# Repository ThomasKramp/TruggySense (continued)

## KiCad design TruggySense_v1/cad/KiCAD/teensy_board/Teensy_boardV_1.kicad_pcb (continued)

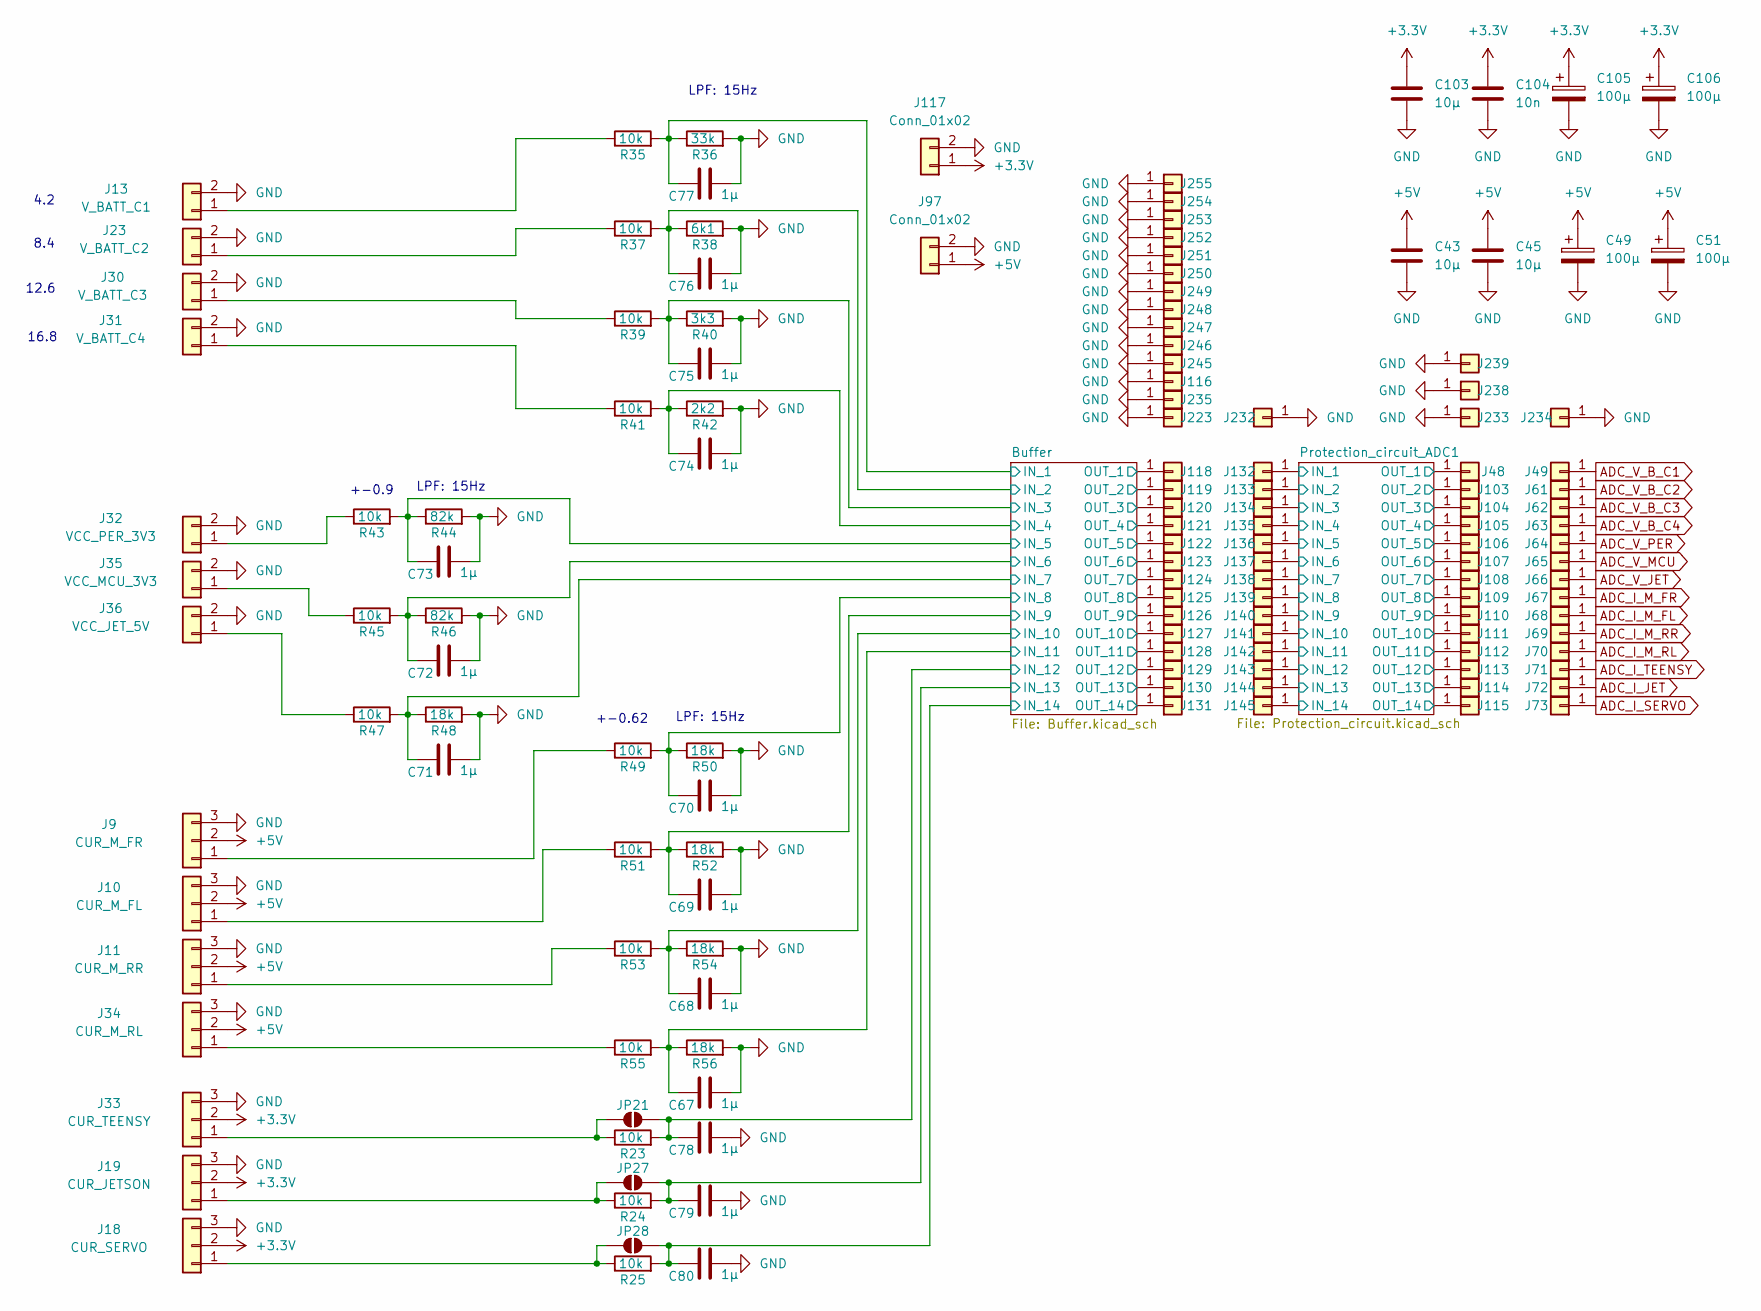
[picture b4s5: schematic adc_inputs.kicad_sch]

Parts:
C43, C45, C103: 10µ; C_0805_2012Metric_Pad1.18x1.45mm_HandSolder
C49, C51, C105, C106: 100µ; CP_Radial_D5.0mm_P2.00mm
C67, C68, C69, C70, C71, C72, C73, C74, C75, C76, C77, C78, C79, C80: 1µ; C_0805_2012Metric_Pad1.18x1.45mm_HandSolder
C104: 10n; C_0805_2012Metric_Pad1.18x1.45mm_HandSolder
J9: CUR_M_FR; PinHeader_1x03_P2.54mm_Vertical
J10: CUR_M_FL; PinHeader_1x03_P2.54mm_Vertical
J11: CUR_M_RR; PinHeader_1x03_P2.54mm_Vertical
J13: V_BATT_C1; PinSocket_1x02_P2.54mm_Vertical
J18: CUR_SERVO; PinHeader_1x03_P2.54mm_Vertical
J19: CUR_JETSON; PinHeader_1x03_P2.54mm_Vertical
J23: V_BATT_C2; PinSocket_1x02_P2.54mm_Vertical
J30: V_BATT_C3; PinSocket_1x02_P2.54mm_Vertical
J31: V_BATT_C4; PinSocket_1x02_P2.54mm_Vertical
J32: VCC_PER_3V3; PinSocket_1x02_P2.54mm_Vertical
J33: CUR_TEENSY; PinHeader_1x03_P2.54mm_Vertical
J34: CUR_M_RL; PinHeader_1x03_P2.54mm_Vertical
J35: VCC_MCU_3V3; PinSocket_1x02_P2.54mm_Vertical
J36: VCC_JET_5V; PinSocket_1x02_P2.54mm_Vertical
J48, J49, J61, J62, J63, J64, J65, J66, J67, J68, J69, J70, J71, J72, J73, J103, J104, J105, J106, J107, J108, J109, J110, J111, J112, J113, J114, J115, J116, J118, J119, J120, J121, J122, J123, J124, J125, J126, J127, J128, J129, J130, J131, J132, J133, J134, J135, J136, J137, J138, J139, J140, J141, J142, J143, J144, J145, J223, J232, J233, J234, J235, J238, J239, J245, J246, J247, J248, J249, J250, J251, J252, J253, J254, J255: Conn_01x01; PinHeader_1x01_P2.54mm_Vertical
J97, J117: Conn_01x02; PinSocket_1x02_P2.54mm_Vertical
JP21, JP27, JP28: SolderJumper_2_Open; SolderJumper-2_P1.3mm_Open_RoundedPad1.0x1.5mm
R23, R24, R25, R35, R37, R39, R41, R43, R45, R47, R49, R51, R53, R55: 10k; R_0805_2012Metric_Pad1.20x1.40mm_HandSolder
R36: 33k; R_0805_2012Metric_Pad1.20x1.40mm_HandSolder
R38: 6k1; R_0805_2012Metric_Pad1.20x1.40mm_HandSolder
R40: 3k3; R_0805_2012Metric_Pad1.20x1.40mm_HandSolder
R42: 2k2; R_0805_2012Metric_Pad1.20x1.40mm_HandSolder
R44, R46: 82k; R_0805_2012Metric_Pad1.20x1.40mm_HandSolder
R48, R50, R52, R54, R56: 18k; R_0805_2012Metric_Pad1.20x1.40mm_HandSolder

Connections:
+5V: C43.1, C45.1, C49.1, C51.1, J9.2, J10.2, J11.2, J34.2, J97.1; also elsewhere on the board
/ADC inputs/Buffer/IN_1: C77.2, R35.2, R36.1; also elsewhere on the board
/ADC inputs/Buffer/IN_2: C76.2, R37.2, R38.1; also elsewhere on the board
/ADC inputs/Buffer/IN_3: C75.2, R39.2, R40.1; also elsewhere on the board
/ADC inputs/Buffer/IN_4: C74.2, R41.2, R42.1; also elsewhere on the board
/ADC inputs/Buffer/IN_5: C73.2, R43.2, R44.1; also elsewhere on the board
/ADC inputs/Buffer/IN_6: C72.2, R45.2, R46.1; also elsewhere on the board
/ADC inputs/Buffer/IN_7: C71.2, R47.2, R48.1; also elsewhere on the board
/ADC inputs/Buffer/IN_8: C70.2, R49.2, R50.1; also elsewhere on the board
/ADC inputs/Buffer/IN_9: C69.2, R51.2, R52.1; also elsewhere on the board
/ADC inputs/Buffer/IN_10: C68.2, R53.2, R54.1; also elsewhere on the board
/ADC inputs/Buffer/IN_11: C67.2, R55.2, R56.1; also elsewhere on the board
/ADC inputs/Buffer/IN_12: C78.2, JP21.2 (B), R23.2; also elsewhere on the board
/ADC inputs/Buffer/IN_13: C79.2, JP27.2 (B), R24.2; also elsewhere on the board
/ADC inputs/Buffer/IN_14: C80.2, JP28.2 (B), R25.2; also elsewhere on the board
/ADC inputs/Buffer/OUT_1: J118.1; also elsewhere on the board
/ADC inputs/Buffer/OUT_2: J119.1; also elsewhere on the board
/ADC inputs/Buffer/OUT_3: J120.1; also elsewhere on the board
/ADC inputs/Buffer/OUT_4: J121.1; also elsewhere on the board
/ADC inputs/Buffer/OUT_5: J122.1; also elsewhere on the board
/ADC inputs/Buffer/OUT_6: J123.1; also elsewhere on the board
/ADC inputs/Buffer/OUT_7: J124.1; also elsewhere on the board
/ADC inputs/Buffer/OUT_8: J125.1; also elsewhere on the board
/ADC inputs/Buffer/OUT_9: J126.1; also elsewhere on the board
/ADC inputs/Buffer/OUT_10: J127.1; also elsewhere on the board
/ADC inputs/Buffer/OUT_11: J128.1; also elsewhere on the board
/ADC inputs/Buffer/OUT_12: J129.1; also elsewhere on the board
/ADC inputs/Buffer/OUT_13: J130.1; also elsewhere on the board
/ADC inputs/Buffer/OUT_14: J131.1; also elsewhere on the board
/ADC inputs/Protection_circuit_ADC1/IN_1: J132.1; also elsewhere on the board
/ADC inputs/Protection_circuit_ADC1/IN_2: J133.1; also elsewhere on the board
/ADC inputs/Protection_circuit_ADC1/IN_3: J134.1; also elsewhere on the board
/ADC inputs/Protection_circuit_ADC1/IN_4: J135.1; also elsewhere on the board
/ADC inputs/Protection_circuit_ADC1/IN_5: J136.1; also elsewhere on the board
/ADC inputs/Protection_circuit_ADC1/IN_6: J137.1; also elsewhere on the board
/ADC inputs/Protection_circuit_ADC1/IN_7: J138.1; also elsewhere on the board
/ADC inputs/Protection_circuit_ADC1/IN_8: J139.1; also elsewhere on the board
/ADC inputs/Protection_circuit_ADC1/IN_9: J140.1; also elsewhere on the board
/ADC inputs/Protection_circuit_ADC1/IN_10: J141.1; also elsewhere on the board
/ADC inputs/Protection_circuit_ADC1/IN_11: J142.1; also elsewhere on the board
/ADC inputs/Protection_circuit_ADC1/IN_12: J143.1; also elsewhere on the board
/ADC inputs/Protection_circuit_ADC1/IN_13: J144.1; also elsewhere on the board
/ADC inputs/Protection_circuit_ADC1/IN_14: J145.1; also elsewhere on the board
/ADC inputs/Protection_circuit_ADC1/OUT_1: J48.1; also elsewhere on the board
/ADC inputs/Protection_circuit_ADC1/OUT_2: J103.1; also elsewhere on the board
/ADC inputs/Protection_circuit_ADC1/OUT_3: J104.1; also elsewhere on the board
/ADC inputs/Protection_circuit_ADC1/OUT_4: J105.1; also elsewhere on the board
/ADC inputs/Protection_circuit_ADC1/OUT_5: J106.1; also elsewhere on the board
/ADC inputs/Protection_circuit_ADC1/OUT_6: J107.1; also elsewhere on the board
/ADC inputs/Protection_circuit_ADC1/OUT_7: J108.1; also elsewhere on the board
/ADC inputs/Protection_circuit_ADC1/OUT_8: J109.1; also elsewhere on the board
/ADC inputs/Protection_circuit_ADC1/OUT_9: J110.1; also elsewhere on the board
/ADC inputs/Protection_circuit_ADC1/OUT_10: J111.1; also elsewhere on the board
/ADC inputs/Protection_circuit_ADC1/OUT_11: J112.1; also elsewhere on the board
/ADC inputs/Protection_circuit_ADC1/OUT_12: J113.1; also elsewhere on the board
/ADC inputs/Protection_circuit_ADC1/OUT_13: J114.1; also elsewhere on the board
/ADC inputs/Protection_circuit_ADC1/OUT_14: J115.1; also elsewhere on the board
ADC_I_JET: J72.1; also elsewhere on the board
ADC_I_M_FL: J68.1; also elsewhere on the board
ADC_I_M_FR: J67.1; also elsewhere on the board
ADC_I_M_RL: J70.1; also elsewhere on the board
ADC_I_M_RR: J69.1; also elsewhere on the board
ADC_I_SERVO: J73.1; also elsewhere on the board
ADC_I_TEENSY: J71.1; also elsewhere on the board
ADC_V_B_C1: J49.1; also elsewhere on the board
ADC_V_B_C2: J61.1; also elsewhere on the board
ADC_V_B_C3: J62.1; also elsewhere on the board
ADC_V_B_C4: J63.1; also elsewhere on the board
ADC_V_JET: J66.1; also elsewhere on the board
ADC_V_MCU: J65.1; also elsewhere on the board
ADC_V_PER: J64.1; also elsewhere on the board
GND: C43.2, C45.2, C49.2, C51.2, C67.1, C68.1, C69.1, C70.1, C71.1, C72.1, C73.1, C74.1, C75.1, C76.1, C77.1, C78.1, C79.1, C80.1, C103.2, C104.2, C105.2, C106.2, J9.3, J10.3, J11.3, J13.2, J18.3, J19.3, J23.2, J30.2, J31.2, J32.2, J33.3, J34.3, J35.2, J36.2, J97.2, J116.1, J117.2, J223.1, J232.1, J233.1, J234.1, J235.1, J238.1, J239.1, J245.1, J246.1, J247.1, J248.1, J249.1, J250.1, J251.1, J252.1, J253.1, J254.1, J255.1, R36.2, R38.2, R40.2, R42.2, R44.2, R46.2, R48.2, R50.2, R52.2, R54.2, R56.2; also elsewhere on the board
unnamed: J9.1, R49.1
unnamed: J10.1, R51.1
unnamed: J11.1, R53.1
unnamed: J13.1, R35.1
unnamed: J18.1, JP28.1 (A), R25.1
unnamed: J19.1, JP27.1 (A), R24.1
unnamed: J23.1, R37.1
unnamed: J30.1, R39.1
unnamed: J31.1, R41.1
unnamed: J32.1, R43.1
unnamed: J33.1, JP21.1 (A), R23.1
unnamed: J34.1, R55.1
unnamed: J35.1, R45.1
unnamed: J36.1, R47.1

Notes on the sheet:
+-0.62
LPF: 15Hz
+-0.9
12.6
16.8
4.2
8.4

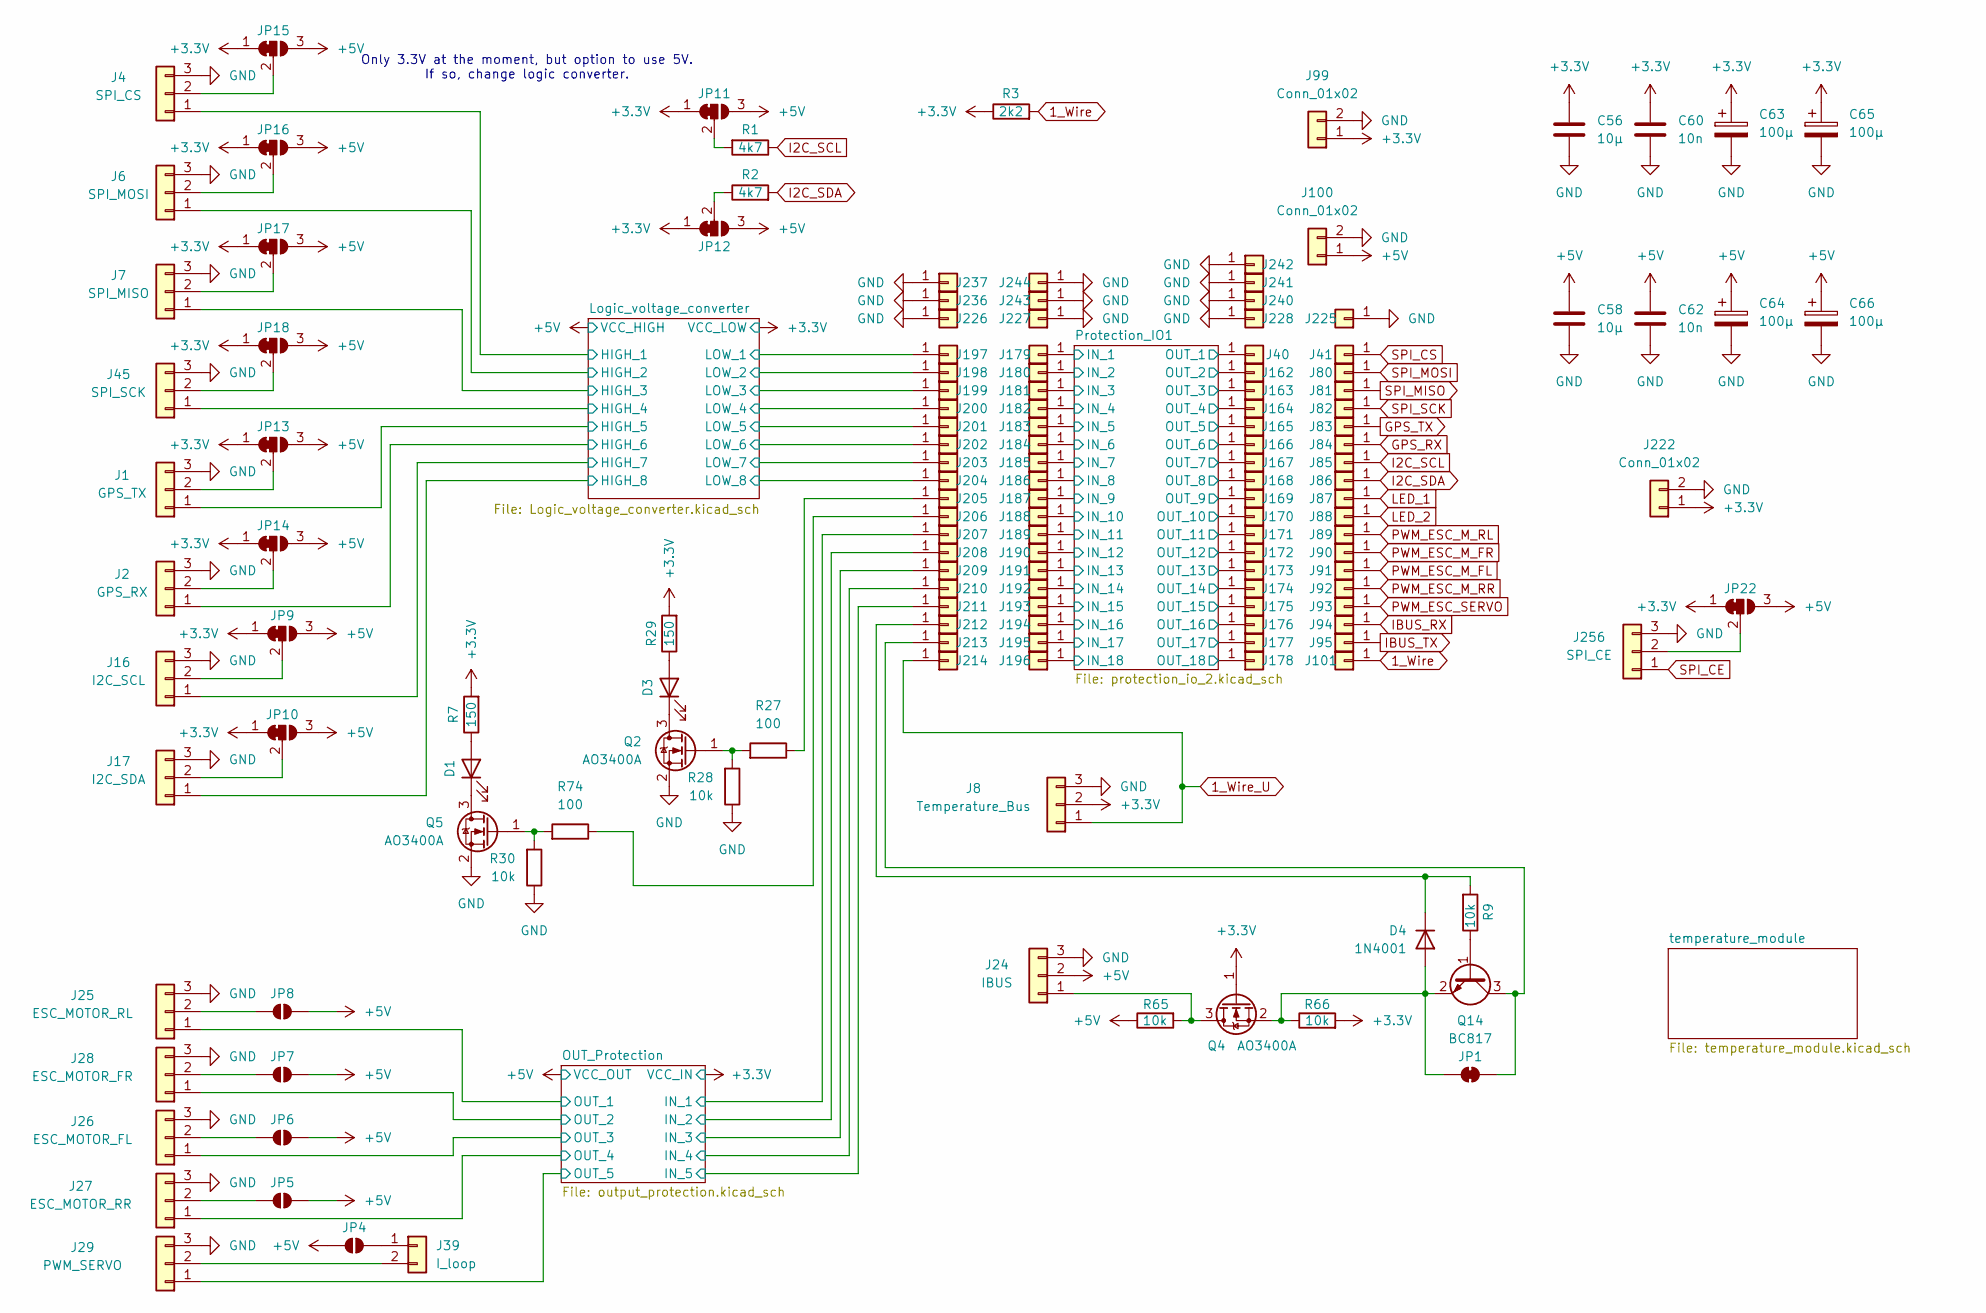
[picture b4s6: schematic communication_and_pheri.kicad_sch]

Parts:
C56, C58: 10µ; C_0805_2012Metric_Pad1.18x1.45mm_HandSolder
C60, C62: 10n; C_0805_2012Metric_Pad1.18x1.45mm_HandSolder
C63, C64, C65, C66: 100µ; CP_Radial_D5.0mm_P2.00mm
D1, D3: LED; LED_0805_2012Metric_Pad1.15x1.40mm_HandSolder
D4: 1N4001; D_SMA_Handsoldering
J1: GPS_TX; PinHeader_1x03_P2.54mm_Vertical
J2: GPS_RX; PinHeader_1x03_P2.54mm_Vertical
J4: SPI_CS; PinHeader_1x03_P2.54mm_Vertical
J6: SPI_MOSI; PinHeader_1x03_P2.54mm_Vertical
J7: SPI_MISO; PinHeader_1x03_P2.54mm_Vertical
J8: Temperature_Bus; PinHeader_1x03_P2.54mm_Vertical
J16: I2C_SCL; PinHeader_1x03_P2.54mm_Vertical
J17: I2C_SDA; PinHeader_1x03_P2.54mm_Vertical
J24: IBUS; PinHeader_1x03_P2.54mm_Vertical
J25: ESC_MOTOR_RL; PinHeader_1x03_P2.54mm_Vertical
J26: ESC_MOTOR_FL; PinHeader_1x03_P2.54mm_Vertical
J27: ESC_MOTOR_RR; PinHeader_1x03_P2.54mm_Vertical
J28: ESC_MOTOR_FR; PinHeader_1x03_P2.54mm_Vertical
J29: PWM_SERVO; PinHeader_1x03_P2.54mm_Vertical
J39: I_loop; PinSocket_1x02_P2.54mm_Vertical
J40, J41, J80, J81, J82, J83, J84, J85, J86, J87, J88, J89, J90, J91, J92, J93, J94, J95, J101, J162, J163, J164, J165, J166, J167, J168, J169, J170, J171, J172, J173, J174, J175, J176, J177, J178, J179, J180, J181, J182, J183, J184, J185, J186, J187, J188, J189, J190, J191, J192, J193, J194, J195, J196, J197, J198, J199, J200, J201, J202, J203, J204, J205, J206, J207, J208, J209, J210, J211, J212, J213, J214, J225, J226, J227, J228, J236, J237, J240, J241, J242, J243, J244: Conn_01x01; PinHeader_1x01_P2.54mm_Vertical
J45: SPI_SCK; PinHeader_1x03_P2.54mm_Vertical
J99, J100, J222: Conn_01x02; PinSocket_1x02_P2.54mm_Vertical
J256: SPI_CE; PinHeader_1x03_P2.54mm_Vertical
JP1: SolderJumper_2_Bridged; SolderJumper-2_P1.3mm_Bridged_RoundedPad1.0x1.5mm
JP4, JP5, JP6, JP7, JP8: SolderJumper_2_Bridged; SolderJumper-2_P1.3mm_Open_RoundedPad1.0x1.5mm
JP9, JP10, JP11, JP12, JP13, JP14, JP15, JP16, JP17, JP18, JP22: SolderJumper_3_Bridged12; SolderJumper-3_P1.3mm_Bridged12_RoundedPad1.0x1.5mm
Q2, Q4, Q5: AO3400A; SOT-23
Q14: BC817; SOT-23
R1, R2: 4k7; R_0805_2012Metric_Pad1.20x1.40mm_HandSolder
R3: 2k2; R_0805_2012Metric_Pad1.20x1.40mm_HandSolder
R7, R29: 150; R_0805_2012Metric_Pad1.20x1.40mm_HandSolder
R9, R28, R30, R65, R66: 10k; R_0805_2012Metric_Pad1.20x1.40mm_HandSolder
R27, R74: 100; R_0805_2012Metric_Pad1.20x1.40mm_HandSolder

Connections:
1_Wire: J101.1, R3.2; also elsewhere on the board
1_Wire_U: J8.1, J214.1; also elsewhere on the board
+5V: C58.1, C62.1, C64.1, C66.1, J24.2, J100.1, J256.2, JP4.1 (A), JP5.2 (B), JP6.2 (B), JP7.2 (B), JP8.2 (B), JP9.3 (B), JP10.3 (B), JP11.3 (B), JP12.3 (B), JP13.3 (B), JP14.3 (B), JP15.3 (B), JP16.3 (B), JP17.3 (B), JP18.3 (B), JP22.2 (B), JP22.3 (B), R65.1; also elsewhere on the board
/Communication & pheripherals/Logic_voltage_converter/HIGH_1: J4.1; also elsewhere on the board
/Communication & pheripherals/Logic_voltage_converter/HIGH_2: J6.1; also elsewhere on the board
/Communication & pheripherals/Logic_voltage_converter/HIGH_3: J7.1; also elsewhere on the board
/Communication & pheripherals/Logic_voltage_converter/HIGH_4: J45.1; also elsewhere on the board
/Communication & pheripherals/Logic_voltage_converter/HIGH_5: J1.1; also elsewhere on the board
/Communication & pheripherals/Logic_voltage_converter/HIGH_6: J2.1; also elsewhere on the board
/Communication & pheripherals/Logic_voltage_converter/HIGH_7: J16.1; also elsewhere on the board
/Communication & pheripherals/Logic_voltage_converter/HIGH_8: J17.1; also elsewhere on the board
/Communication & pheripherals/Logic_voltage_converter/LOW_1: J197.1; also elsewhere on the board
/Communication & pheripherals/Logic_voltage_converter/LOW_2: J198.1; also elsewhere on the board
/Communication & pheripherals/Logic_voltage_converter/LOW_3: J199.1; also elsewhere on the board
/Communication & pheripherals/Logic_voltage_converter/LOW_4: J200.1; also elsewhere on the board
/Communication & pheripherals/Logic_voltage_converter/LOW_5: J201.1; also elsewhere on the board
/Communication & pheripherals/Logic_voltage_converter/LOW_6: J202.1; also elsewhere on the board
/Communication & pheripherals/Logic_voltage_converter/LOW_7: J203.1; also elsewhere on the board
/Communication & pheripherals/Logic_voltage_converter/LOW_8: J204.1; also elsewhere on the board
/Communication & pheripherals/OUT_Protection/IN_1: J207.1; also elsewhere on the board
/Communication & pheripherals/OUT_Protection/IN_2: J208.1; also elsewhere on the board
/Communication & pheripherals/OUT_Protection/IN_3: J209.1; also elsewhere on the board
/Communication & pheripherals/OUT_Protection/IN_4: J210.1; also elsewhere on the board
/Communication & pheripherals/OUT_Protection/IN_5: J211.1; also elsewhere on the board
/Communication & pheripherals/OUT_Protection/OUT_1: J25.1; also elsewhere on the board
/Communication & pheripherals/OUT_Protection/OUT_2: J28.1; also elsewhere on the board
/Communication & pheripherals/OUT_Protection/OUT_3: J26.1; also elsewhere on the board
/Communication & pheripherals/OUT_Protection/OUT_4: J27.1; also elsewhere on the board
/Communication & pheripherals/OUT_Protection/OUT_5: J29.1; also elsewhere on the board
/Communication & pheripherals/Protection_IO1/IN_1: J179.1; also elsewhere on the board
/Communication & pheripherals/Protection_IO1/IN_2: J180.1; also elsewhere on the board
/Communication & pheripherals/Protection_IO1/IN_3: J181.1; also elsewhere on the board
/Communication & pheripherals/Protection_IO1/IN_4: J182.1; also elsewhere on the board
/Communication & pheripherals/Protection_IO1/IN_5: J183.1; also elsewhere on the board
/Communication & pheripherals/Protection_IO1/IN_6: J184.1; also elsewhere on the board
/Communication & pheripherals/Protection_IO1/IN_7: J185.1; also elsewhere on the board
/Communication & pheripherals/Protection_IO1/IN_8: J186.1; also elsewhere on the board
/Communication & pheripherals/Protection_IO1/IN_9: J187.1; also elsewhere on the board
/Communication & pheripherals/Protection_IO1/IN_10: J188.1; also elsewhere on the board
/Communication & pheripherals/Protection_IO1/IN_11: J189.1; also elsewhere on the board
/Communication & pheripherals/Protection_IO1/IN_12: J190.1; also elsewhere on the board
/Communication & pheripherals/Protection_IO1/IN_13: J191.1; also elsewhere on the board
/Communication & pheripherals/Protection_IO1/IN_14: J192.1; also elsewhere on the board
/Communication & pheripherals/Protection_IO1/IN_15: J193.1; also elsewhere on the board
/Communication & pheripherals/Protection_IO1/IN_16: J194.1; also elsewhere on the board
/Communication & pheripherals/Protection_IO1/IN_17: J195.1; also elsewhere on the board
/Communication & pheripherals/Protection_IO1/IN_18: J196.1; also elsewhere on the board
/Communication & pheripherals/Protection_IO1/OUT_1: J40.1; also elsewhere on the board
/Communication & pheripherals/Protection_IO1/OUT_2: J162.1; also elsewhere on the board
/Communication & pheripherals/Protection_IO1/OUT_3: J163.1; also elsewhere on the board
/Communication & pheripherals/Protection_IO1/OUT_4: J164.1; also elsewhere on the board
/Communication & pheripherals/Protection_IO1/OUT_5: J165.1; also elsewhere on the board
/Communication & pheripherals/Protection_IO1/OUT_6: J166.1; also elsewhere on the board
/Communication & pheripherals/Protection_IO1/OUT_7: J167.1; also elsewhere on the board
/Communication & pheripherals/Protection_IO1/OUT_8: J168.1; also elsewhere on the board
/Communication & pheripherals/Protection_IO1/OUT_9: J169.1; also elsewhere on the board
/Communication & pheripherals/Protection_IO1/OUT_10: J170.1; also elsewhere on the board
/Communication & pheripherals/Protection_IO1/OUT_11: J171.1; also elsewhere on the board
/Communication & pheripherals/Protection_IO1/OUT_12: J172.1; also elsewhere on the board
/Communication & pheripherals/Protection_IO1/OUT_13: J173.1; also elsewhere on the board
/Communication & pheripherals/Protection_IO1/OUT_14: J174.1; also elsewhere on the board
/Communication & pheripherals/Protection_IO1/OUT_15: J175.1; also elsewhere on the board
/Communication & pheripherals/Protection_IO1/OUT_16: J176.1; also elsewhere on the board
/Communication & pheripherals/Protection_IO1/OUT_17: J177.1; also elsewhere on the board
/Communication & pheripherals/Protection_IO1/OUT_18: J178.1; also elsewhere on the board
GND: C56.2, C58.2, C60.2, C62.2, C63.2, C64.2, C65.2, C66.2, J1.3, J2.3, J4.3, J6.3, J7.3, J8.3, J16.3, J17.3, J24.3, J25.3, J26.3, J27.3, J28.3, J29.3, J45.3, J99.2, J100.2, J222.2, J225.1, J226.1, J227.1, J228.1, J236.1, J237.1, J240.1, J241.1, J242.1, J243.1, J244.1, J256.3, Q2.2 (S), Q5.2 (S), R28.1, R30.1; also elsewhere on the board
GPS_RX: J84.1; also elsewhere on the board
GPS_TX: J83.1; also elsewhere on the board
I2C_SCL: J85.1, R1.1; also elsewhere on the board
I2C_SDA: J86.1, R2.2; also elsewhere on the board
IBUS_RX: J94.1; also elsewhere on the board
IBUS_TX: J95.1; also elsewhere on the board
unnamed: D1.2 (A), R7.1
unnamed: D1.1 (K), Q5.3 (D)
unnamed: D3.2 (A), R29.1
unnamed: D3.1 (K), Q2.3 (D)
unnamed: D4.2 (A), JP1.2 (B), Q4.2 (S), Q14.2 (E), R66.1
unnamed: D4.1 (K), J212.1, R9.2
unnamed: J1.2, JP13.2 (C)
unnamed: J2.2, JP14.2 (C)
unnamed: J4.2, JP15.2 (C)
unnamed: J6.2, JP16.2 (C)
unnamed: J7.2, JP17.2 (C)
unnamed: J16.2, JP9.2 (C)
unnamed: J17.2, JP10.2 (C)
unnamed: J24.1, Q4.3 (D), R65.2
unnamed: J25.2, JP8.1 (A)
unnamed: J26.2, JP6.1 (A)
unnamed: J27.2, JP5.1 (A)
unnamed: J28.2, JP7.1 (A)
unnamed: J29.2, J39.2
unnamed: J39.1, JP4.2 (B)
unnamed: J45.2, JP18.2 (C)
unnamed: J205.1, R27.1
unnamed: J206.1, R74.1
unnamed: J213.1, JP1.1 (A), Q14.3 (C)
unnamed: JP11.2 (C), R1.2
unnamed: JP12.2 (C), R2.1
unnamed: Q2.1 (G), R27.2, R28.2
unnamed: Q5.1 (G), R30.2, R74.2
unnamed: Q14.1 (B), R9.1
PWM_ESC_M_FL: J91.1; also elsewhere on the board
PWM_ESC_M_FR: J90.1; also elsewhere on the board
PWM_ESC_M_RL: J89.1; also elsewhere on the board
PWM_ESC_M_RR: J92.1; also elsewhere on the board
PWM_ESC_SERVO: J93.1; also elsewhere on the board
SPI_CS: J41.1; also elsewhere on the board
SPI_MISO: J81.1; also elsewhere on the board
SPI_MOSI: J80.1; also elsewhere on the board
SPI_SCK: J82.1; also elsewhere on the board

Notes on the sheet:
Only 3.3V at the moment, but option to use 5V. If so, change logic converter.

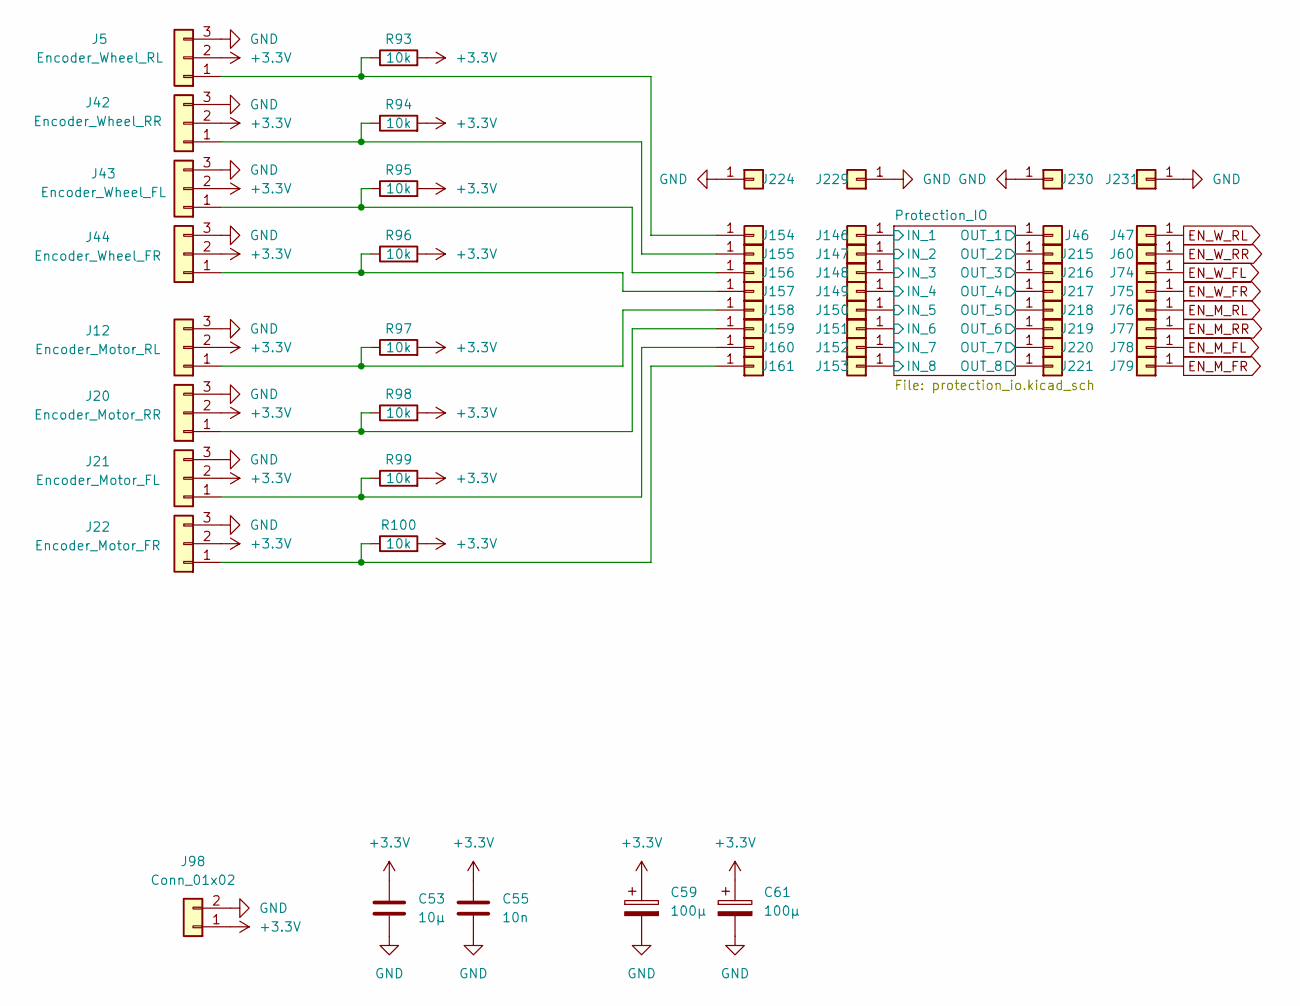
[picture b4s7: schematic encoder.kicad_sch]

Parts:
C53: 10µ; C_0805_2012Metric_Pad1.18x1.45mm_HandSolder
C55: 10n; C_0805_2012Metric_Pad1.18x1.45mm_HandSolder
C59, C61: 100µ; CP_Radial_D5.0mm_P2.00mm
J5: Encoder_Wheel_RL; PinHeader_1x03_P2.54mm_Vertical
J12: Encoder_Motor_RL; PinHeader_1x03_P2.54mm_Vertical
J20: Encoder_Motor_RR; PinHeader_1x03_P2.54mm_Vertical
J21: Encoder_Motor_FL; PinHeader_1x03_P2.54mm_Vertical
J22: Encoder_Motor_FR; PinHeader_1x03_P2.54mm_Vertical
J42: Encoder_Wheel_RR; PinHeader_1x03_P2.54mm_Vertical
J43: Encoder_Wheel_FL; PinHeader_1x03_P2.54mm_Vertical
J44: Encoder_Wheel_FR; PinHeader_1x03_P2.54mm_Vertical
J46, J47, J60, J74, J75, J76, J77, J78, J79, J146, J147, J148, J149, J150, J151, J152, J153, J154, J155, J156, J157, J158, J159, J160, J161, J215, J216, J217, J218, J219, J220, J221, J224, J229, J230, J231: Conn_01x01; PinHeader_1x01_P2.54mm_Vertical
J98: Conn_01x02; PinSocket_1x02_P2.54mm_Vertical
R93, R94, R95, R96, R97, R98, R99, R100: 10k; R_0805_2012Metric

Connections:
/Encoder/Protection_IO/IN_1: J146.1; also elsewhere on the board
/Encoder/Protection_IO/IN_2: J147.1; also elsewhere on the board
/Encoder/Protection_IO/IN_3: J148.1; also elsewhere on the board
/Encoder/Protection_IO/IN_4: J149.1; also elsewhere on the board
/Encoder/Protection_IO/IN_5: J150.1; also elsewhere on the board
/Encoder/Protection_IO/IN_6: J151.1; also elsewhere on the board
/Encoder/Protection_IO/IN_7: J152.1; also elsewhere on the board
/Encoder/Protection_IO/IN_8: J153.1; also elsewhere on the board
/Encoder/Protection_IO/OUT_1: J46.1; also elsewhere on the board
/Encoder/Protection_IO/OUT_2: J215.1; also elsewhere on the board
/Encoder/Protection_IO/OUT_3: J216.1; also elsewhere on the board
/Encoder/Protection_IO/OUT_4: J217.1; also elsewhere on the board
/Encoder/Protection_IO/OUT_5: J218.1; also elsewhere on the board
/Encoder/Protection_IO/OUT_6: J219.1; also elsewhere on the board
/Encoder/Protection_IO/OUT_7: J220.1; also elsewhere on the board
/Encoder/Protection_IO/OUT_8: J221.1; also elsewhere on the board
EN_M_FL: J78.1; also elsewhere on the board
EN_M_FR: J79.1; also elsewhere on the board
EN_M_RL: J76.1; also elsewhere on the board
EN_M_RR: J77.1; also elsewhere on the board
EN_W_FL: J74.1; also elsewhere on the board
EN_W_FR: J75.1; also elsewhere on the board
EN_W_RL: J47.1; also elsewhere on the board
EN_W_RR: J60.1; also elsewhere on the board
GND: C53.2, C55.2, C59.2, C61.2, J5.3, J12.3, J20.3, J21.3, J22.3, J42.3, J43.3, J44.3, J98.2, J224.1, J229.1, J230.1, J231.1; also elsewhere on the board
unnamed: J12.1, J158.1, R97.1
unnamed: J5.1, J154.1, R93.1
unnamed: J42.1, J155.1, R94.1
unnamed: J43.1, J156.1, R95.1
unnamed: J44.1, J157.1, R96.1
unnamed: J20.1, J159.1, R98.1
unnamed: J21.1, J160.1, R99.1
unnamed: J22.1, J161.1, R100.1

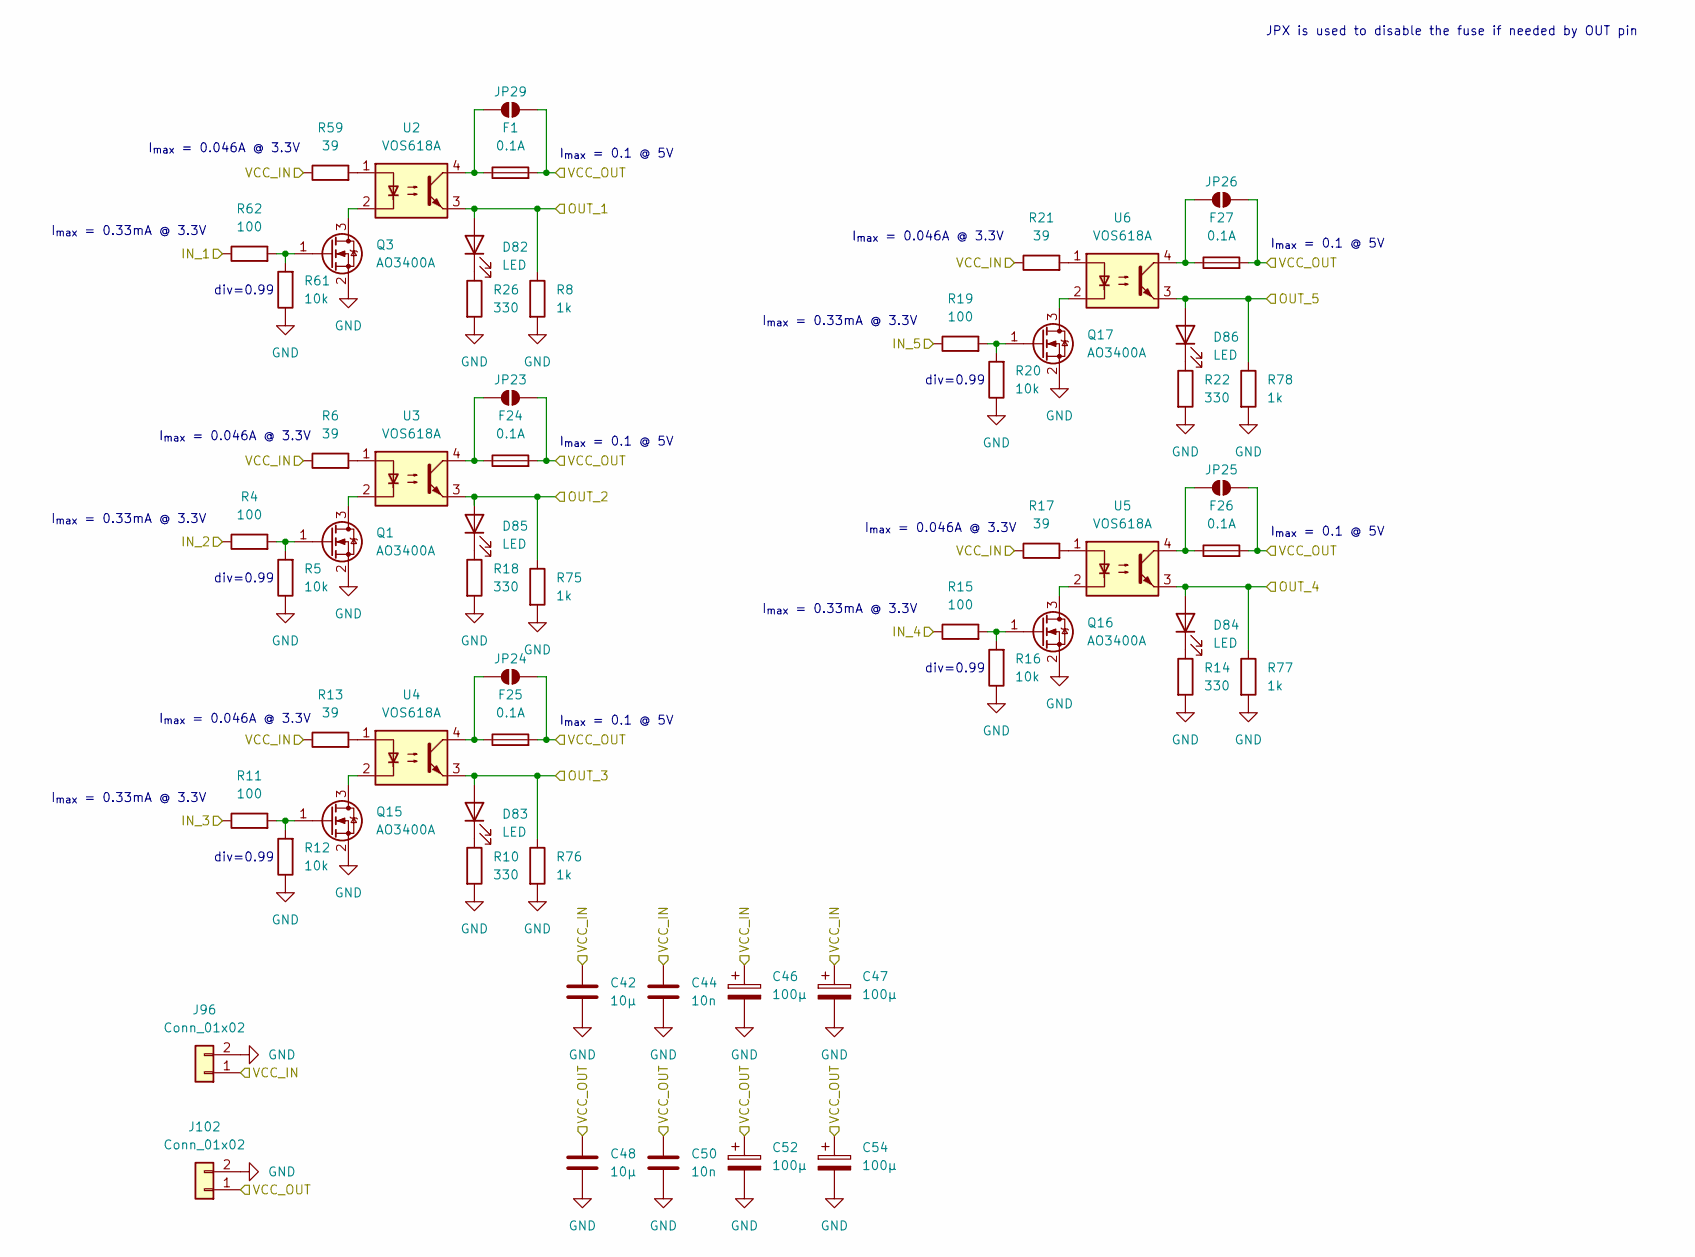
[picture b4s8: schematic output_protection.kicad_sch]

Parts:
C42, C48: 10µ; C_0805_2012Metric_Pad1.18x1.45mm_HandSolder
C44, C50: 10n; C_0805_2012Metric_Pad1.18x1.45mm_HandSolder
C46, C47, C52, C54: 100µ; CP_Radial_D5.0mm_P2.00mm
D82, D83, D84, D85, D86: LED; LED_0805_2012Metric_Pad1.15x1.40mm_HandSolder
F1, F24, F25, F26, F27: 0.1A; Fuse_0805_2012Metric_Pad1.15x1.40mm_HandSolder
J96, J102: Conn_01x02; PinSocket_1x02_P2.54mm_Vertical
JP23, JP24, JP25, JP26, JP29: SolderJumper_2_Open; SolderJumper-2_P1.3mm_Open_RoundedPad1.0x1.5mm
Q1, Q3, Q15, Q16, Q17: AO3400A; SOT-23
R4, R11, R15, R19, R62: 100; R_0805_2012Metric_Pad1.20x1.40mm_HandSolder
R5, R12, R16, R20, R61: 10k; R_0805_2012Metric_Pad1.20x1.40mm_HandSolder
R6, R13, R17, R21, R59: 39; R_0805_2012Metric_Pad1.20x1.40mm_HandSolder
R8, R75, R76, R77, R78: 1k; R_0805_2012Metric_Pad1.20x1.40mm_HandSolder
R10, R14, R18, R22, R26: 330; R_0805_2012Metric_Pad1.20x1.40mm_HandSolder
U2, U3, U4, U5, U6: VOS618A; VO617A

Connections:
+5V: C48.1, C50.1, C52.1, C54.1, F1.2, F24.2, F25.2, F26.2, F27.2, J102.1, JP23.2 (B), JP24.2 (B), JP25.2 (B), JP26.2 (B), JP29.2 (B); also elsewhere on the board
/Communication & pheripherals/OUT_Protection/IN_1: R62.1; also elsewhere on the board
/Communication & pheripherals/OUT_Protection/IN_2: R4.1; also elsewhere on the board
/Communication & pheripherals/OUT_Protection/IN_3: R11.1; also elsewhere on the board
/Communication & pheripherals/OUT_Protection/IN_4: R15.1; also elsewhere on the board
/Communication & pheripherals/OUT_Protection/IN_5: R19.1; also elsewhere on the board
/Communication & pheripherals/OUT_Protection/OUT_1: D82.2 (A), R8.1, U2.3; also elsewhere on the board
/Communication & pheripherals/OUT_Protection/OUT_2: D85.2 (A), R75.1, U3.3; also elsewhere on the board
/Communication & pheripherals/OUT_Protection/OUT_3: D83.2 (A), R76.1, U4.3; also elsewhere on the board
/Communication & pheripherals/OUT_Protection/OUT_4: D84.2 (A), R77.1, U5.3; also elsewhere on the board
/Communication & pheripherals/OUT_Protection/OUT_5: D86.2 (A), R78.1, U6.3; also elsewhere on the board
GND: C42.2, C44.2, C46.2, C47.2, C48.2, C50.2, C52.2, C54.2, J96.2, J102.2, Q1.2 (S), Q3.2 (S), Q15.2 (S), Q16.2 (S), Q17.2 (S), R5.1, R8.2, R10.2, R12.1, R14.2, R16.1, R18.2, R20.1, R22.2, R26.2, R61.1, R75.2, R76.2, R77.2, R78.2; also elsewhere on the board
unnamed: D82.1 (K), R26.1
unnamed: D83.1 (K), R10.1
unnamed: D84.1 (K), R14.1
unnamed: D85.1 (K), R18.1
unnamed: D86.1 (K), R22.1
unnamed: F24.1, JP23.1 (A), U3.4
unnamed: F25.1, JP24.1 (A), U4.4
unnamed: F26.1, JP25.1 (A), U5.4
unnamed: F27.1, JP26.1 (A), U6.4
unnamed: Q1.3 (D), U3.2
unnamed: Q1.1 (G), R4.2, R5.2
unnamed: Q3.3 (D), U2.2
unnamed: Q3.1 (G), R61.2, R62.2
unnamed: Q15.3 (D), U4.2
unnamed: Q15.1 (G), R11.2, R12.2
unnamed: Q16.3 (D), U5.2
unnamed: Q16.1 (G), R15.2, R16.2
unnamed: Q17.3 (D), U6.2
unnamed: Q17.1 (G), R19.2, R20.2
unnamed: R6.2, U3.1
unnamed: R13.2, U4.1
unnamed: R17.2, U5.1
unnamed: R21.2, U6.1
unnamed: R59.2, U2.1

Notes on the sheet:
I_{max} = 0.1 @ 5V
I_{max} = 0.33mA @ 3.3V
div=0.99
I_{max} = 0.046A @ 3.3V
JPX is used to disable the fuse if needed by OUT pin
